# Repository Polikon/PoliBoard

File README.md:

Hey everyone,
As a first venture into pcb making i've decided to make a 60% that is similar to the phantom, as in you just plug it into a Teensy2++, problem is a 60% has no space for a Teensy, so I just ended up with alot of pins which will be hand wired to the Teensy.

The size of the board and all the holes match the GH60, so it should be compatible with all cases. 

I am looking for someone to check if my wiring is fine. I am also looking for advice as to how to wire the Teensy, as in which of my pins (p0-p43) connects where. As this is the first pcb a scratched together I would appreciate any and all feedback.

Important files:

IS31FL3731 datasheet: http://www.mouser.com/ds/2/198/31FL3731-258525.pdf

IS31FL3731 supplement: http://www.issi.com/WW/pdf/IS31FL3731_App_Note.pdf

Teensy power consumption: https://www.pjrc.com/teensy/low_power.html

Teensy 3.3v guide https://www.pjrc.com/teensy/3volt.html

Formulas:

I=64.7/R_Ext <-- Formula for current in LED charliematrix. Taken from datasheet pg19

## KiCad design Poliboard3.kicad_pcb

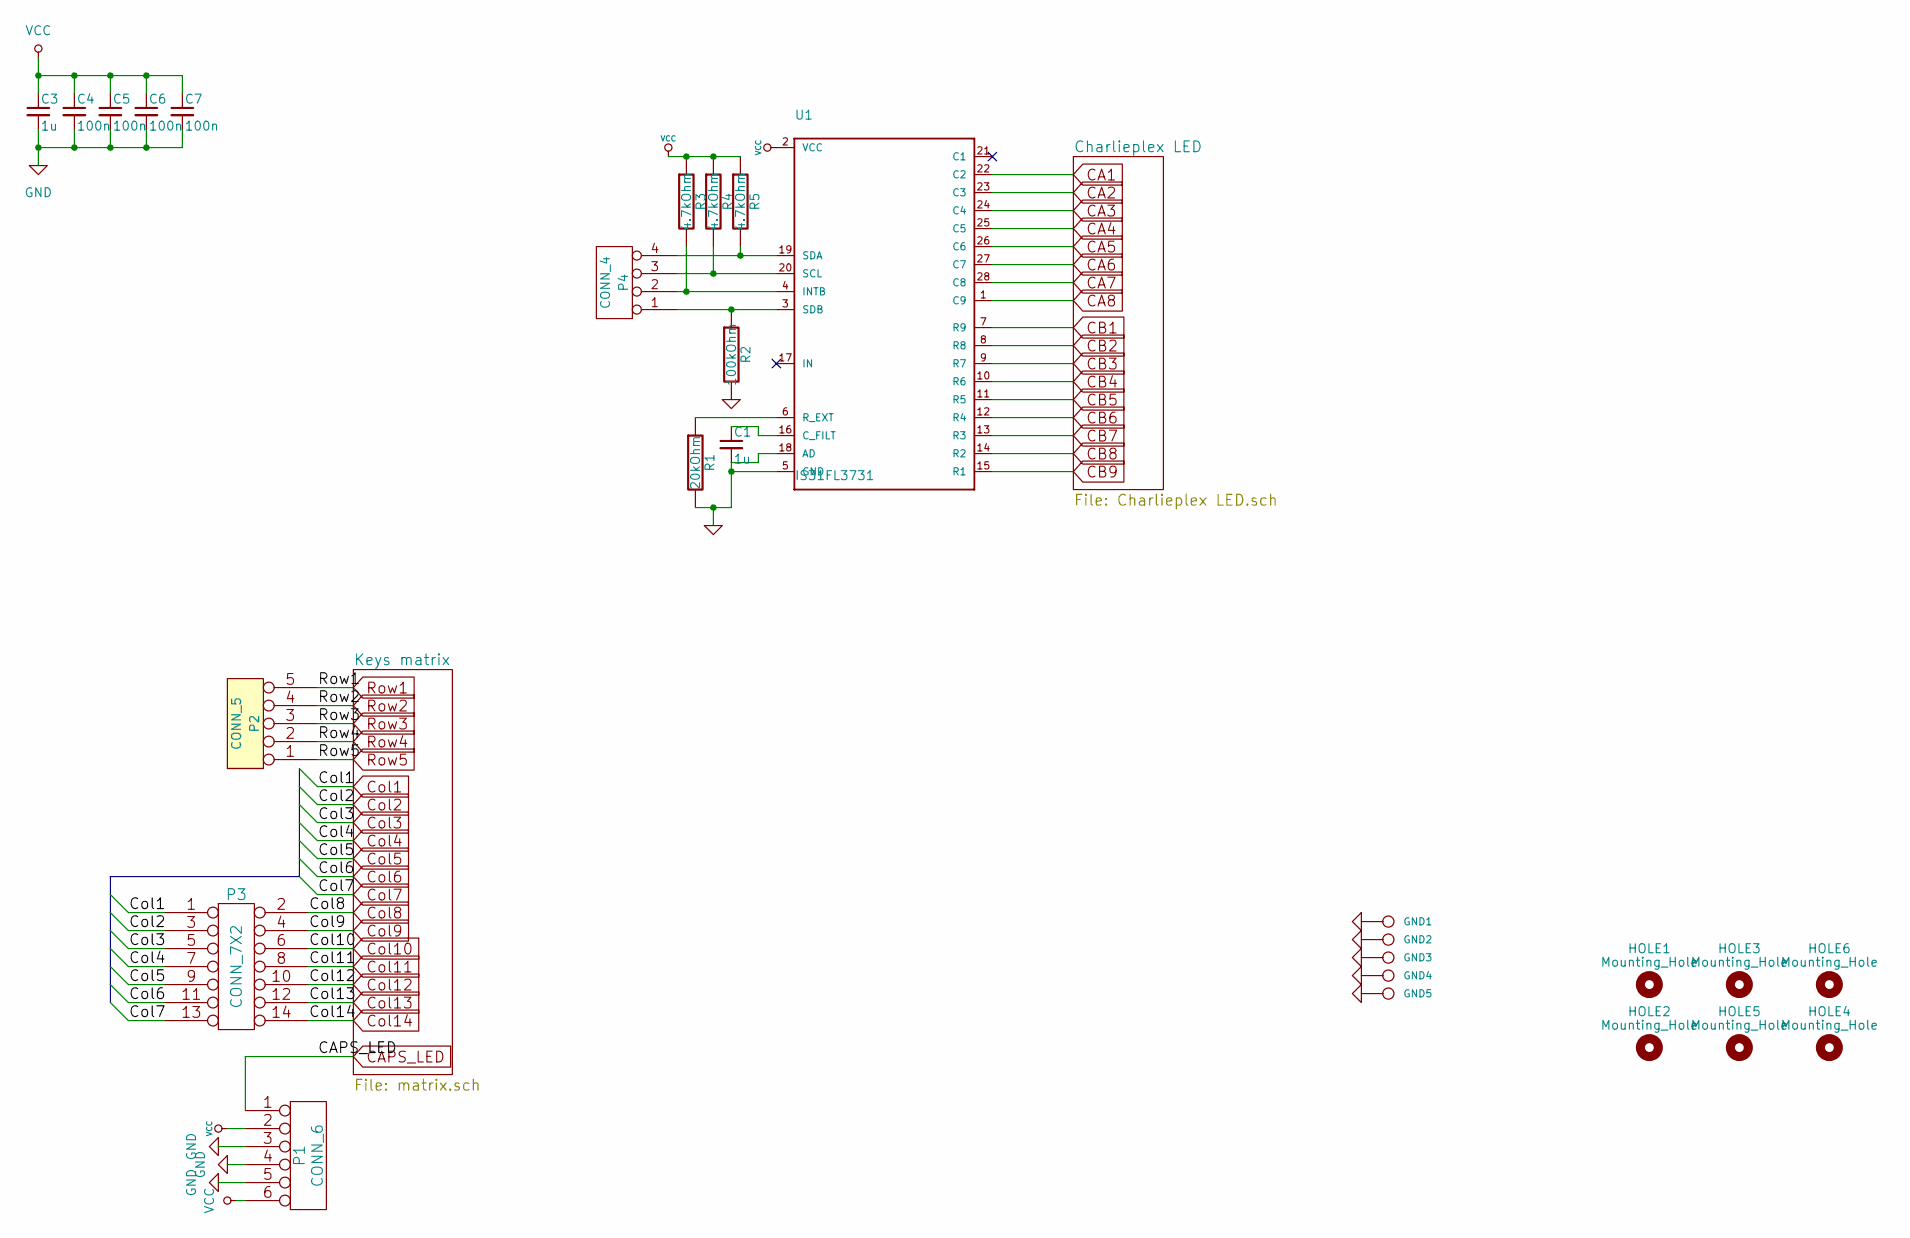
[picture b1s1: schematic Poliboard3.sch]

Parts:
C1, C3: 1u; C_0805_HandSoldering
C4, C5, C6, C7: 100n; C_0805_HandSoldering
GND1, GND2, GND3, GND4, GND5: CONN_1; PIN_1
HOLE1, HOLE2, HOLE3, HOLE4: Mounting_Hole; HOLE1
HOLE5, HOLE6: Mounting_Hole; HOLE2
P1: CONN_6; Pin_Header_Straight_1x06_Pitch1.27mm
P2: CONN_5; Pin_Header_Straight_1x05_Pitch1.27mm
P3: CONN_7X2; Pin_Header_Straight_2x07_Pitch1.27mm
P4: CONN_4; Pin_Header_Straight_1x04_Pitch1.27mm
R1: 20kOhm; R_0805_HandSoldering
R2: 100kOhm; R_0805_HandSoldering
R3, R4, R5: 4.7kOhm; R_0805_HandSoldering
U1: IS31FL3731

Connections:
CA1: U1.22 (C2); also elsewhere on the board
CA2: U1.23 (C3); also elsewhere on the board
CA3: U1.24 (C4); also elsewhere on the board
CA4: U1.25 (C5); also elsewhere on the board
CA5: U1.26 (C6); also elsewhere on the board
CA6: U1.27 (C7); also elsewhere on the board
CA7: U1.28 (C8); also elsewhere on the board
CA8: U1.1 (C9); also elsewhere on the board
CAPS_LED: P1.1; also elsewhere on the board
CB1: U1.7 (R9); also elsewhere on the board
CB2: U1.8 (R8); also elsewhere on the board
CB3: U1.9 (R7); also elsewhere on the board
CB4: U1.10 (R6); also elsewhere on the board
CB5: U1.11 (R5); also elsewhere on the board
CB6: U1.12 (R4); also elsewhere on the board
CB7: U1.13 (R3); also elsewhere on the board
CB8: U1.14 (R2); also elsewhere on the board
CB9: U1.15 (R1); also elsewhere on the board
Col1: P3.1; also elsewhere on the board
Col2: P3.3; also elsewhere on the board
Col3: P3.5; also elsewhere on the board
Col4: P3.7; also elsewhere on the board
Col5: P3.9; also elsewhere on the board
Col6: P3.11; also elsewhere on the board
Col7: P3.13; also elsewhere on the board
Col8: P3.2; also elsewhere on the board
Col9: P3.4; also elsewhere on the board
Col10: P3.6; also elsewhere on the board
Col11: P3.8; also elsewhere on the board
Col12: P3.10; also elsewhere on the board
Col13: P3.12; also elsewhere on the board
Col14: P3.14; also elsewhere on the board
GND: C1.2, C3.2, C4.2, C5.2, C6.2, C7.2, GND1.1, GND2.1, GND3.1, GND4.1, GND5.1, P1.3, P1.4, P1.5, R1.2, R2.2, U1.5 (GND), U1.18 (AD)
unnamed: C1.1, U1.16 (C_FILT)
unnamed: P4.1, R2.1, U1.3 (SDB)
unnamed: P4.2, R3.2, U1.4 (INTB)
unnamed: P4.3, R4.2, U1.20 (SCL)
unnamed: P4.4, R5.2, U1.19 (SDA)
unnamed: R1.1, U1.6 (R_EXT)
Row1: P2.5; also elsewhere on the board
Row2: P2.4; also elsewhere on the board
Row3: P2.3; also elsewhere on the board
Row4: P2.2; also elsewhere on the board
Row5: P2.1; also elsewhere on the board
VCC: C3.1, C4.1, C5.1, C6.1, C7.1, P1.2, P1.6, R3.1, R4.1, R5.1, U1.2 (VCC); also elsewhere on the board

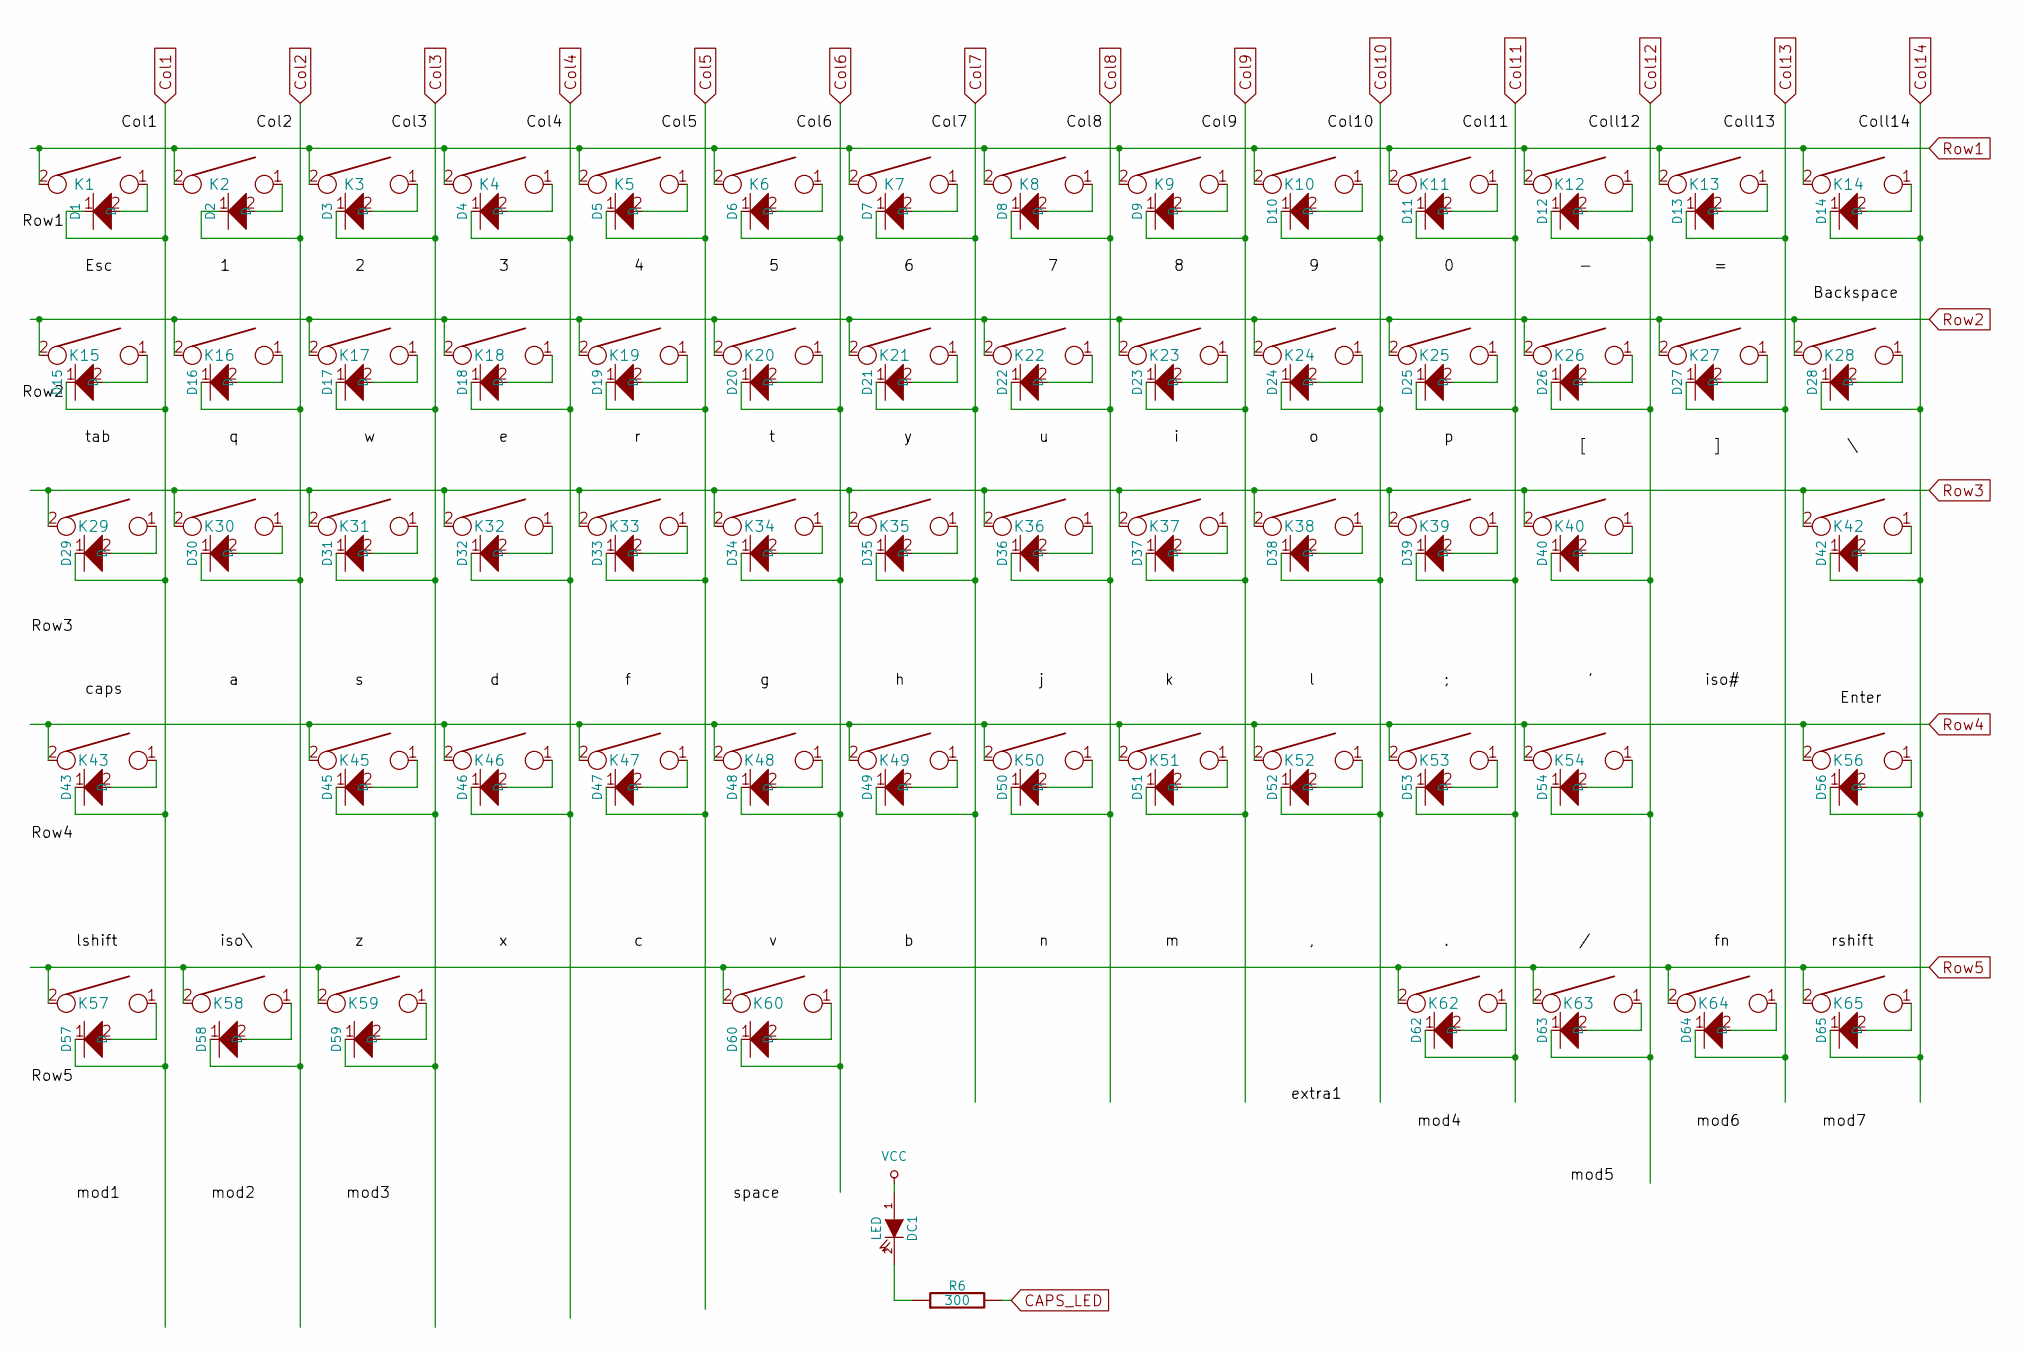
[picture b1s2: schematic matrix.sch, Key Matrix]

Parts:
D1, D2, D3, D4, D5, D6, D7, D8, D9, D10, D11, D12, D13, D14, D15, D16, D17, D18, D19, D20, D21, D22, D23, D24, D25, D26, D27, D28, D29, D30, D31, D32, D33, D34, D35, D36, D37, D38, D39, D40, D42, D43, D45, D46, D47, D48, D49, D50, D51, D52, D53, D54, D56, D57, D58, D59, D60, D62, D63, D64, D65: D; D_SOD123_axial
DC1: LED; MX1A-led_no3d
K1, K2, K3, K4, K5, K6, K7, K8, K9, K10, K11, K12, K13, K16, K17, K18, K19, K20, K21, K22, K23, K24, K25, K26, K27, K30, K31, K32, K33, K34, K35, K36, K37, K38, K39, K40, K45, K46, K47, K48, K49, K50, K51, K52, K53, K54: KEYSW; CHERRY_PCB_100H
K14: KEYSW; CHERRY_PCB_200H
K15, K28: KEYSW; CHERRY_PCB_150H
K29: KEYSW; CHERRY_PCB_175H
K42, K43: KEYSW; CHERRY_PCB_225H
K56: KEYSW; CHERRY_PCB_275H
K57, K58, K59, K62, K63, K64, K65: KEYSW; CHERRY_PCB_125H
K60: KEYSW; CHERRY_PCB_625H
R6: 300; R_0805_HandSoldering

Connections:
CAPS_LED: R6.2; also elsewhere on the board
Col1: D1.1, D15.1, D29.1, D43.1, D57.1; also elsewhere on the board
Col2: D2.1, D16.1, D30.1, D58.1; also elsewhere on the board
Col3: D3.1, D17.1, D31.1, D45.1, D59.1; also elsewhere on the board
Col4: D4.1, D18.1, D32.1, D46.1; also elsewhere on the board
Col5: D5.1, D19.1, D33.1, D47.1; also elsewhere on the board
Col6: D6.1, D20.1, D34.1, D48.1, D60.1; also elsewhere on the board
Col7: D7.1, D21.1, D35.1, D49.1; also elsewhere on the board
Col8: D8.1, D22.1, D36.1, D50.1; also elsewhere on the board
Col9: D9.1, D23.1, D37.1, D51.1; also elsewhere on the board
Col10: D10.1, D24.1, D38.1, D52.1; also elsewhere on the board
Col11: D11.1, D25.1, D39.1, D53.1, D62.1; also elsewhere on the board
Col12: D12.1, D26.1, D40.1, D54.1, D63.1; also elsewhere on the board
Col13: D13.1, D27.1, D64.1; also elsewhere on the board
Col14: D14.1, D28.1, D42.1, D56.1, D65.1; also elsewhere on the board
unnamed: D1.2, K1.1
unnamed: D2.2, K2.1
unnamed: D3.2, K3.1
unnamed: D4.2, K4.1
unnamed: D5.2, K5.1
unnamed: D6.2, K6.1
unnamed: D7.2, K7.1
unnamed: D8.2, K8.1
unnamed: D9.2, K9.1
unnamed: D10.2, K10.1
unnamed: D11.2, K11.1
unnamed: D12.2, K12.1
unnamed: D13.2, K13.1
unnamed: D14.2, K14.1
unnamed: D15.2, K15.1
unnamed: D16.2, K16.1
unnamed: D17.2, K17.1
unnamed: D18.2, K18.1
unnamed: D19.2, K19.1
unnamed: D20.2, K20.1
unnamed: D21.2, K21.1
unnamed: D22.2, K22.1
unnamed: D23.2, K23.1
unnamed: D24.2, K24.1
unnamed: D25.2, K25.1
unnamed: D26.2, K26.1
unnamed: D27.2, K27.1
unnamed: D28.2, K28.1
unnamed: D29.2, K29.1
unnamed: D30.2, K30.1
unnamed: D31.2, K31.1
unnamed: D32.2, K32.1
unnamed: D33.2, K33.1
unnamed: D34.2, K34.1
unnamed: D35.2, K35.1
unnamed: D36.2, K36.1
unnamed: D37.2, K37.1
unnamed: D38.2, K38.1
unnamed: D39.2, K39.1
unnamed: D40.2, K40.1
unnamed: D42.2, K42.1
unnamed: D43.2, K43.1
unnamed: D45.2, K45.1
unnamed: D46.2, K46.1
unnamed: D47.2, K47.1
unnamed: D48.2, K48.1
unnamed: D49.2, K49.1
unnamed: D50.2, K50.1
unnamed: D51.2, K51.1
unnamed: D52.2, K52.1
unnamed: D53.2, K53.1
unnamed: D54.2, K54.1
unnamed: D56.2, K56.1
unnamed: D57.2, K57.1
unnamed: D58.2, K58.1
unnamed: D59.2, K59.1
unnamed: D60.2, K60.1
unnamed: D62.2, K62.1
unnamed: D63.2, K63.1
unnamed: D64.2, K64.1
unnamed: D65.2, K65.1
unnamed: DC1.2 (K), R6.1
Row1: K1.2, K2.2, K3.2, K4.2, K5.2, K6.2, K7.2, K8.2, K9.2, K10.2, K11.2, K12.2, K13.2, K14.2; also elsewhere on the board
Row2: K15.2, K16.2, K17.2, K18.2, K19.2, K20.2, K21.2, K22.2, K23.2, K24.2, K25.2, K26.2, K27.2, K28.2; also elsewhere on the board
Row3: K29.2, K30.2, K31.2, K32.2, K33.2, K34.2, K35.2, K36.2, K37.2, K38.2, K39.2, K40.2, K42.2; also elsewhere on the board
Row4: K43.2, K45.2, K46.2, K47.2, K48.2, K49.2, K50.2, K51.2, K52.2, K53.2, K54.2, K56.2; also elsewhere on the board
Row5: K57.2, K58.2, K59.2, K60.2, K62.2, K63.2, K64.2, K65.2; also elsewhere on the board
VCC: DC1.1 (A); also elsewhere on the board

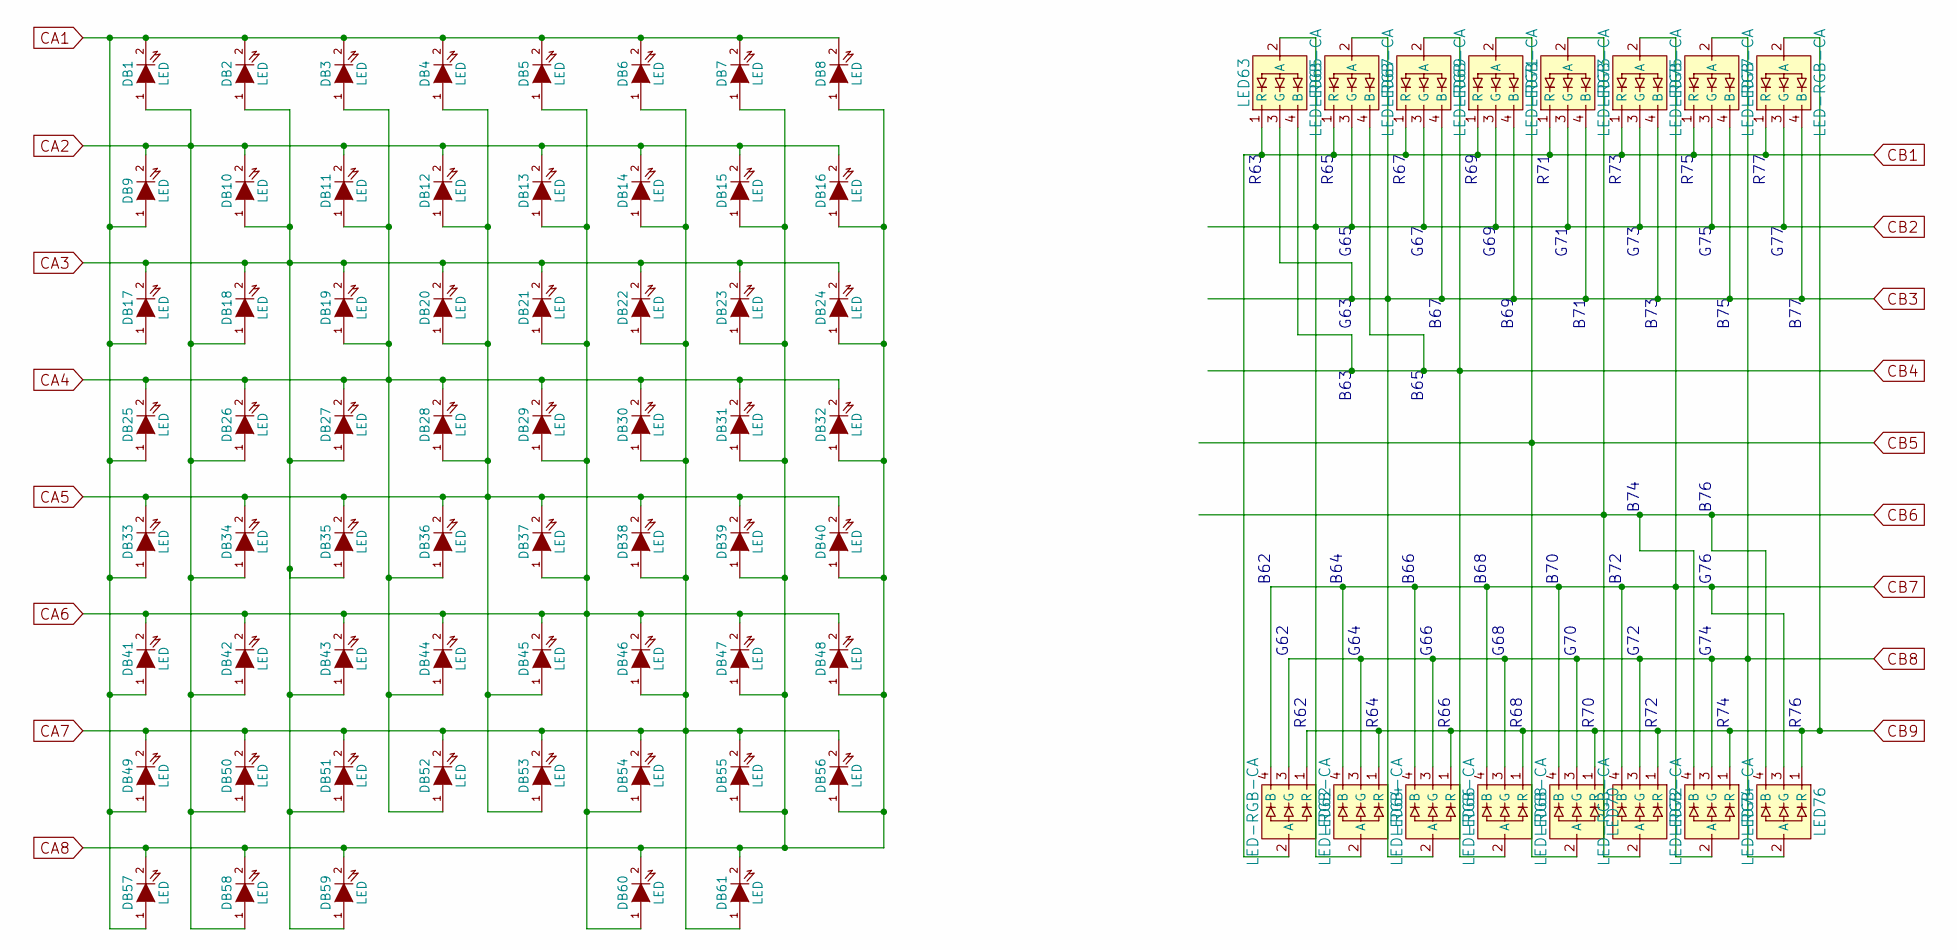
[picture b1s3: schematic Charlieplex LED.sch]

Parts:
DB1, DB2, DB3, DB4, DB5, DB6, DB7, DB8, DB9, DB10, DB11, DB12, DB13, DB14, DB15, DB16, DB17, DB18, DB19, DB20, DB21, DB22, DB23, DB24, DB25, DB26, DB27, DB28, DB29, DB30, DB31, DB32, DB33, DB34, DB35, DB36, DB37, DB38, DB39, DB40, DB41, DB42, DB43, DB44, DB45, DB46, DB47, DB48, DB49, DB50, DB51, DB52, DB53, DB54, DB55, DB56, DB57, DB58, DB59, DB60, DB61: LED; MX1A-led_no3d
LED62, LED63, LED64, LED65, LED66, LED67, LED68, LED69, LED70, LED71, LED72, LED73, LED74, LED75, LED76, LED77: LED-RGB-CA; LED_D5.0mm-4

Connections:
CA1: DB1.2 (K), DB2.2 (K), DB3.2 (K), DB4.2 (K), DB5.2 (K), DB6.2 (K), DB7.2 (K), DB8.2 (K), DB9.1 (A), DB17.1 (A), DB25.1 (A), DB33.1 (A), DB41.1 (A), DB49.1 (A), DB57.1 (A); also elsewhere on the board
CA2: DB1.1 (A), DB9.2 (K), DB10.2 (K), DB11.2 (K), DB12.2 (K), DB13.2 (K), DB14.2 (K), DB15.2 (K), DB16.2 (K), DB18.1 (A), DB26.1 (A), DB34.1 (A), DB42.1 (A), DB50.1 (A), DB58.1 (A); also elsewhere on the board
CA3: DB2.1 (A), DB10.1 (A), DB17.2 (K), DB18.2 (K), DB19.2 (K), DB20.2 (K), DB21.2 (K), DB22.2 (K), DB23.2 (K), DB24.2 (K), DB27.1 (A), DB35.1 (A), DB43.1 (A), DB51.1 (A), DB59.1 (A); also elsewhere on the board
CA4: DB3.1 (A), DB11.1 (A), DB19.1 (A), DB25.2 (K), DB26.2 (K), DB27.2 (K), DB28.2 (K), DB29.2 (K), DB30.2 (K), DB31.2 (K), DB32.2 (K), DB36.1 (A), DB44.1 (A), DB52.1 (A); also elsewhere on the board
CA5: DB4.1 (A), DB12.1 (A), DB20.1 (A), DB28.1 (A), DB33.2 (K), DB34.2 (K), DB35.2 (K), DB36.2 (K), DB37.2 (K), DB38.2 (K), DB39.2 (K), DB40.2 (K), DB45.1 (A), DB53.1 (A); also elsewhere on the board
CA6: DB5.1 (A), DB13.1 (A), DB21.1 (A), DB29.1 (A), DB37.1 (A), DB41.2 (K), DB42.2 (K), DB43.2 (K), DB44.2 (K), DB45.2 (K), DB46.2 (K), DB47.2 (K), DB48.2 (K), DB54.1 (A), DB60.1 (A); also elsewhere on the board
CA7: DB6.1 (A), DB14.1 (A), DB22.1 (A), DB30.1 (A), DB38.1 (A), DB46.1 (A), DB49.2 (K), DB50.2 (K), DB51.2 (K), DB52.2 (K), DB53.2 (K), DB54.2 (K), DB55.2 (K), DB56.2 (K), DB61.1 (A); also elsewhere on the board
CA8: DB7.1 (A), DB8.1 (A), DB15.1 (A), DB16.1 (A), DB23.1 (A), DB24.1 (A), DB31.1 (A), DB32.1 (A), DB39.1 (A), DB40.1 (A), DB47.1 (A), DB48.1 (A), DB55.1 (A), DB56.1 (A), DB57.2 (K), DB58.2 (K), DB59.2 (K), DB60.2 (K), DB61.2 (K); also elsewhere on the board
CB1: LED62.2 (A), LED63.1 (R), LED65.1 (R), LED67.1 (R), LED69.1 (R), LED71.1 (R), LED73.1 (R), LED75.1 (R), LED77.1 (R); also elsewhere on the board
CB2: LED63.2 (A), LED64.2 (A), LED65.3 (G), LED67.3 (G), LED69.3 (G), LED71.3 (G), LED73.3 (G), LED75.3 (G), LED77.3 (G); also elsewhere on the board
CB3: LED63.3 (G), LED65.2 (A), LED66.2 (A), LED67.4 (B), LED69.4 (B), LED71.4 (B), LED73.4 (B), LED75.4 (B), LED77.4 (B); also elsewhere on the board
CB4: LED63.4 (B), LED65.4 (B), LED67.2 (A), LED68.2 (A); also elsewhere on the board
CB5: LED69.2 (A), LED70.2 (A); also elsewhere on the board
CB6: LED71.2 (A), LED72.2 (A), LED74.4 (B), LED76.4 (B); also elsewhere on the board
CB7: LED62.4 (B), LED64.4 (B), LED66.4 (B), LED68.4 (B), LED70.4 (B), LED72.4 (B), LED73.2 (A), LED74.2 (A), LED76.3 (G); also elsewhere on the board
CB8: LED62.3 (G), LED64.3 (G), LED66.3 (G), LED68.3 (G), LED70.3 (G), LED72.3 (G), LED74.3 (G), LED75.2 (A), LED76.2 (A); also elsewhere on the board
CB9: LED62.1 (R), LED64.1 (R), LED66.1 (R), LED68.1 (R), LED70.1 (R), LED72.1 (R), LED74.1 (R), LED76.1 (R), LED77.2 (A); also elsewhere on the board

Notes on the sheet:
R63
G63
B63
R65
G65
B65
B67
B69
B71
B73
B75
B77
G67
R67
R69
R71
R73
R75
R77
G69
G71
G73
G75
G77
R76
G76
B76
B74
G74
R74
R72
G72
B72
B70
B68
B66
B64
B62
G62
R62

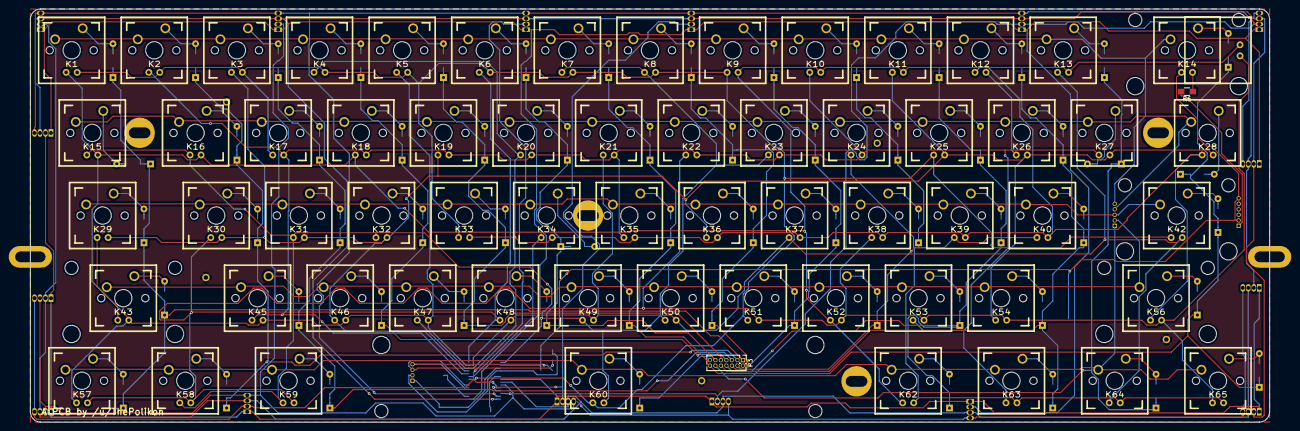
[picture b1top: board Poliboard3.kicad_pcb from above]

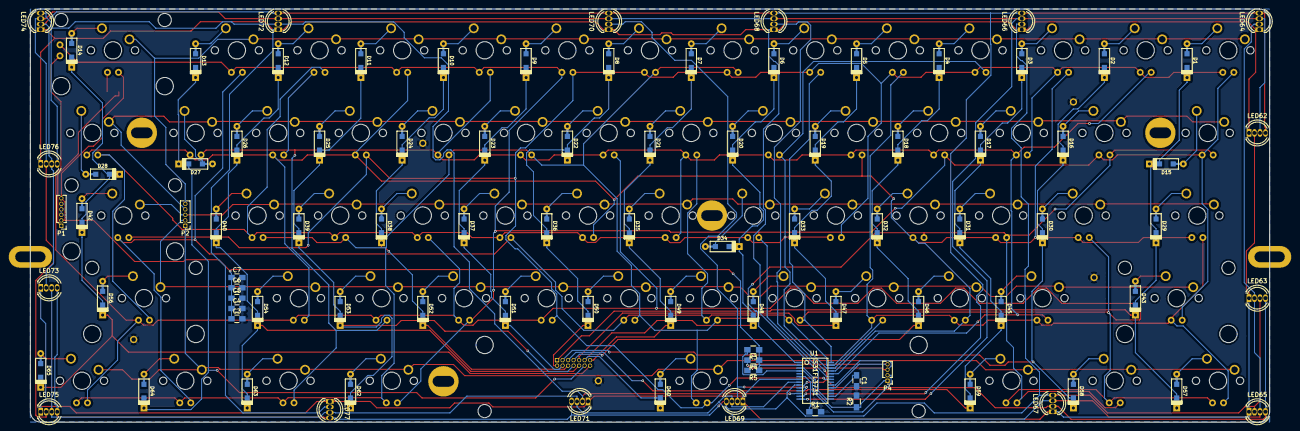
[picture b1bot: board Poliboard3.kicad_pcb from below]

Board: 2 copper layers, 285.8 x 95.3 mm, 228 parts (92 on the bottom side), 107 nets.
